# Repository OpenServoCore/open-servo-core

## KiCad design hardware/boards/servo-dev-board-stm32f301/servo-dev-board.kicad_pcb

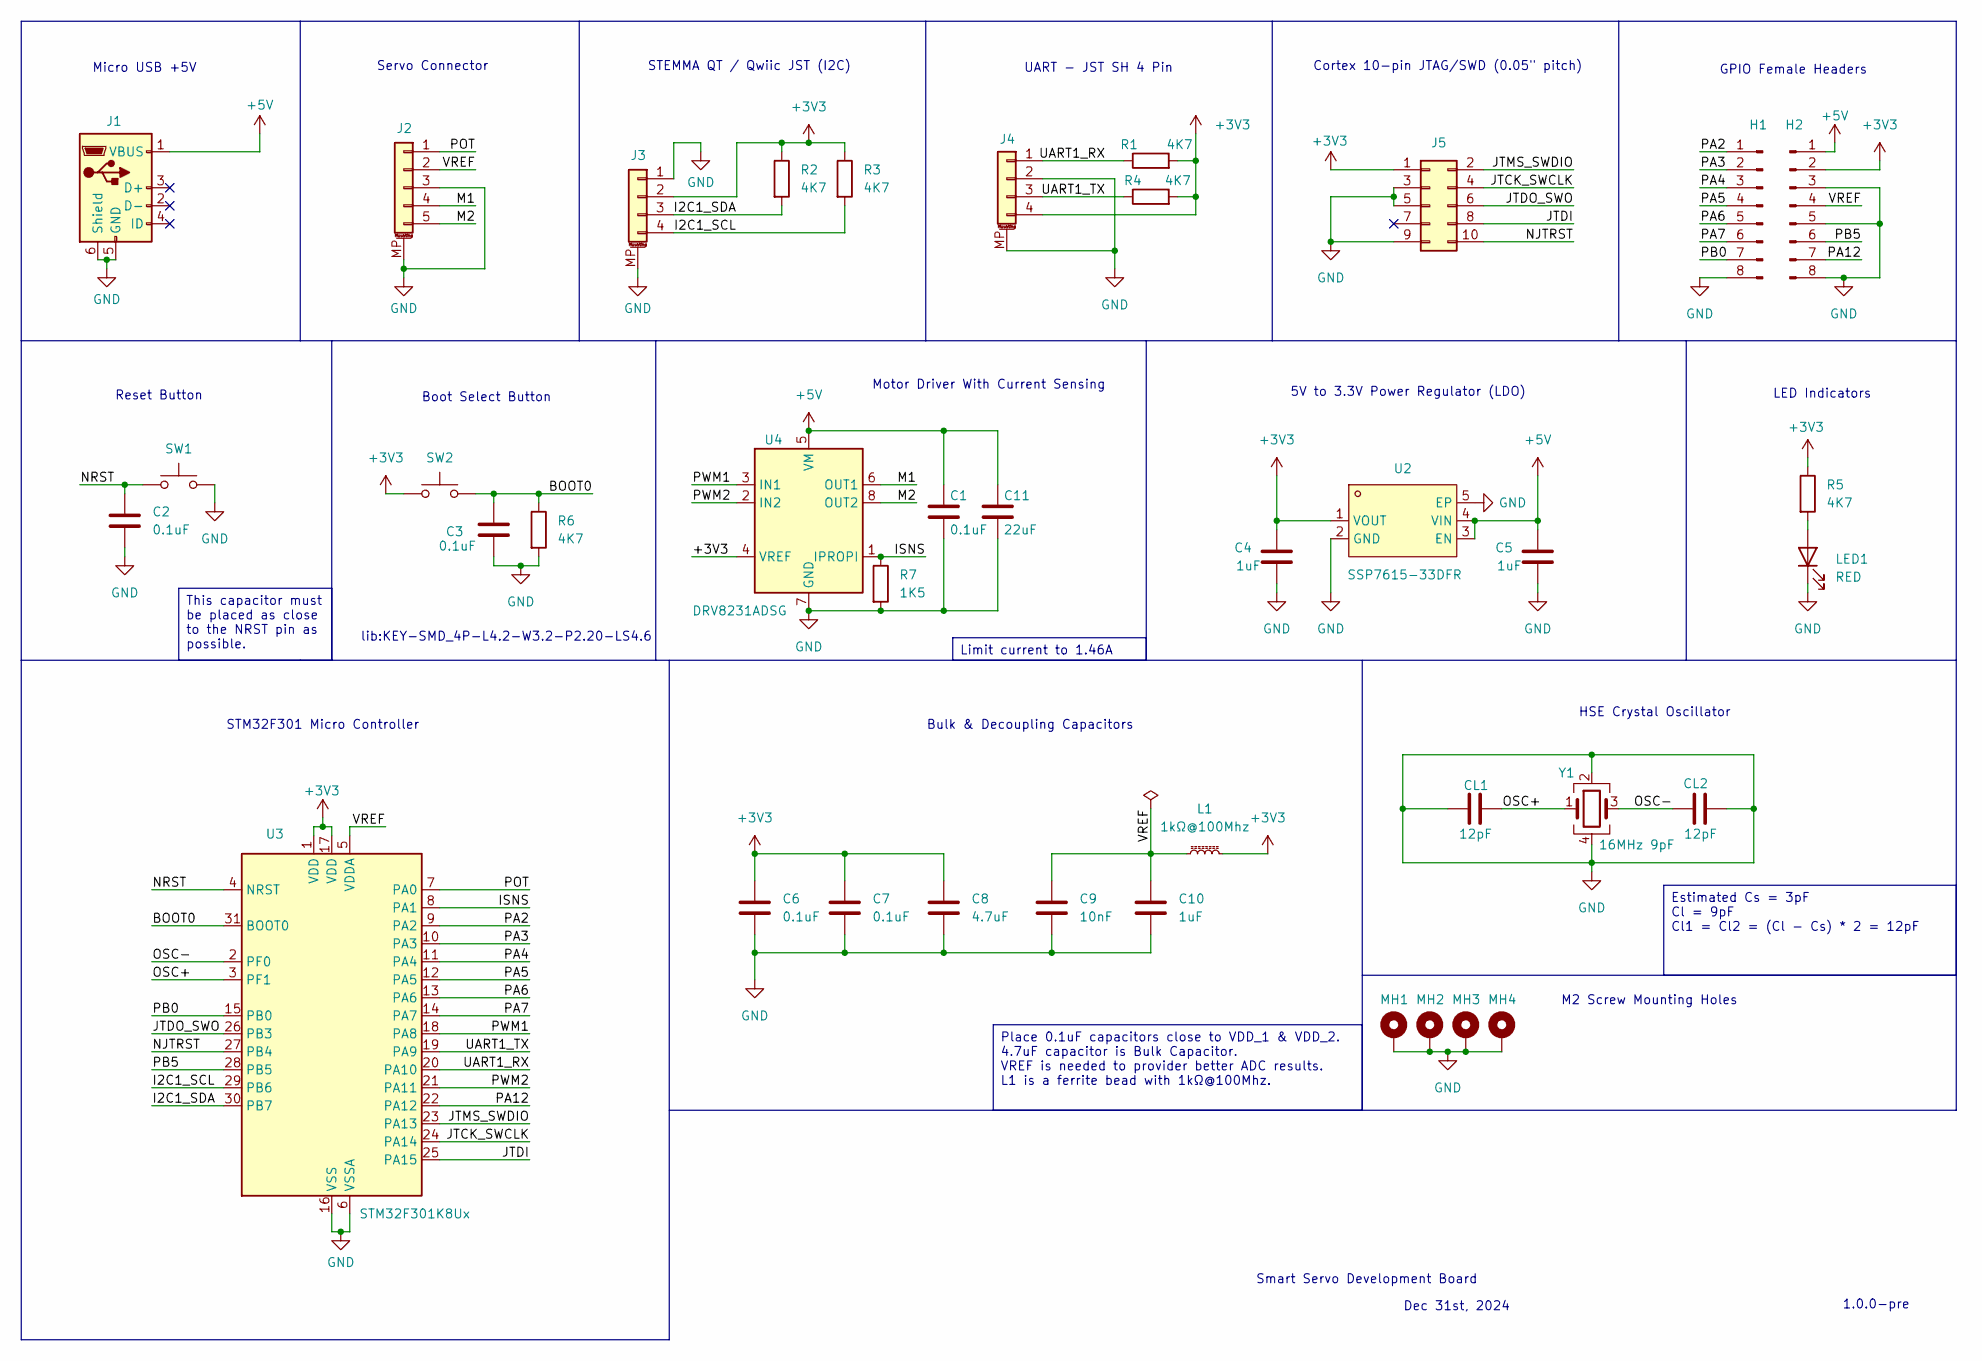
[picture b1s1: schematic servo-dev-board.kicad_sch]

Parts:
C1, C2, C3, C6, C7: 0.1uF; C_0402_1005Metric; LCSC C1525
C4, C5, C10: 1uF; C_0402_1005Metric; LCSC C52923
C8: 4.7uF; C_0603_1608Metric; LCSC C19666
C9: 10nF; C_0402_1005Metric; LCSC C15195
C11: 22uF; C_0603_1608Metric; LCSC C59461
CL1, CL2: 12pF; C_0402_1005Metric; LCSC C1547
H1, H2: Conn_01x08_Pin; PinHeader_1x08_P2.54mm_Vertical; LCSC C6332201
J1: USB_B_Micro; USB_Micro-B_Amphenol_10118194-0001LF_Horizontal; LCSC C428495
J2: Conn_01x05_MountingPin; JST_ZH_B5B-ZR-SM4-TF_1x05-1MP_P1.50mm_Vertical; LCSC C265440
J3, J4: Conn_01x04_MountingPin; JST_SH_BM04B-SRSS-TB_1x04-1MP_P1.00mm_Vertical; LCSC C160390
J5: Conn_02x05_Odd_Even; IDC-TH_10P-P1.27-X1270WV-2X05A-6TV01; LCSC C2962225
L1: 1kΩ@100Mhz; L_0402_1005Metric; LCSC C76883
LED1: RED; LED_0603_1608Metric; LCSC C2286
MH1, MH2, MH3, MH4: MountingHole_Pad_MP; MountingHole_2.2mm_M2_Pad_Via
R1, R2, R3, R4, R5, R6: 4K7; R_0402_1005Metric; LCSC C25792
R7: 1K5; R_0402_1005Metric; LCSC C25867
SW1, SW2: SW_Push; SW_SPST_PTS810; LCSC C221895
U2: SSP7615-33DFR; UDFN-4-1EP_1x1mm_P0.65mm_EP0.48x0.48mm; LCSC Part C3011523
U3: STM32F301K8Ux; QFN-32-1EP_5x5mm_P0.5mm_EP3.45x3.45mm; LCSC C111684
U4: DRV8231ADSG; WSON-8-1EP_2x2mm_P0.5mm_EP0.9x1.6mm
Y1: 16MHz 9pF; Crystal_SMD_3225-4Pin_3.2x2.5mm; LCSC C13738

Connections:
+3V3: C4.2, C6.2, C7.2, C8.2, H2.2, J3.2, J4.4, J5.1, L1.2, R1.2, R2.1, R3.1, R4.2, R5.1, SW2.1, U2.1 (VOUT), U3.1 (VDD), U3.17 (VDD), U4.4 (VREF)
+5V: C1.2, C5.2, C11.2, H2.1, J1.1 (VBUS), U2.3 (EN), U2.4 (VIN), U4.5 (VM)
/BOOT0: C3.1, R6.1, SW2.2, U3.31 (BOOT0)
/I2C1_SCL: J3.4, R3.2, U3.29 (PB6)
/I2C1_SDA: J3.3, R2.2, U3.30 (PB7)
/ISNS: R7.1, U3.8 (PA1), U4.1 (IPROPI)
/JTCK_SWCLK: J5.4, U3.24 (PA14)
/JTDI: J5.8, U3.25 (PA15)
/JTDO_SWO: J5.6, U3.26 (PB3)
/JTMS_SWDIO: J5.2, U3.23 (PA13)
/M1: J2.4, U4.6 (OUT1)
/M2: J2.5, U4.8 (OUT2)
/NJTRST: J5.10, U3.27 (PB4)
/NRST: C2.2, SW1.1, U3.4 (NRST)
/OSC+: CL1.1, U3.3 (PF1), Y1.1
/OSC-: CL2.2, U3.2 (PF0), Y1.3
/PA2: H1.1, U3.9 (PA2)
/PA3: H1.2, U3.10 (PA3)
/PA4: H1.3, U3.11 (PA4)
/PA5: H1.4, U3.12 (PA5)
/PA6: H1.5, U3.13 (PA6)
/PA7: H1.6, U3.14 (PA7)
/PA12: H2.7, U3.22 (PA12)
/PB0: H1.7, U3.15 (PB0)
/PB5: H2.6, U3.28 (PB5)
/POT: J2.1, U3.7 (PA0)
/PWM1: U3.18 (PA8), U4.3 (IN1)
/PWM2: U3.21 (PA11), U4.2 (IN2)
/UART1_RX: J4.1, R1.1, U3.20 (PA10)
/UART1_TX: J4.3, R4.1, U3.19 (PA9)
/VREF: C9.2, C10.2, H2.4, J2.2, L1.1, U3.5 (VDDA)
GND: C1.1, C2.1, C3.2, C4.1, C5.1, C6.1, C7.1, C8.1, C9.1, C10.1, C11.1, CL1.2, CL2.1, H1.8, H2.3, H2.5, H2.8, J1.5 (GND), J1.6 (Shield), J2.3, J2.MP (MountPin), J3.1, J3.MP (MountPin), J4.2, J4.MP (MountPin), J5.3, J5.5, J5.9, LED1.1 (K), MH1.1, MH2.1, MH3.1, MH4.1, R6.2, R7.2, SW1.2, U2.2 (GND), U2.5 (EP), U3.6 (VSSA), U3.16 (VSS), U3.32 (VSS), U3.33 (VSS), U4.7 (GND), U4.9 (GND), Y1.2, Y1.4
unnamed: LED1.2 (A), R5.2

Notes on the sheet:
Cortex 10-pin JTAG/SWD (0.05" pitch)
Dec 31st, 2024
Reset Button
Smart Servo Development Board
STM32F301 Micro Controller
Boot Select Button
Servo Connector
Bulk & Decoupling Capacitors
GPIO Female Headers
1.0.0-pre
5V to 3.3V Power Regulator (LDO)
LED Indicators
Micro USB +5V
M2 Screw Mounting Holes
UART - JST SH 4 Pin
STEMMA QT / Qwiic JST (I2C)
HSE Crystal Oscillator
lib:KEY-SMD_4P-L4.2-W3.2-P2.20-LS4.6
Motor Driver With Current Sensing
This capacitor must be placed as close to the NRST pin as possible.
Place 0.1uF capacitors close to VDD_1 & VDD_2. 4.7uF capacitor is Bulk Capacitor. VREF is needed to provider better ADC results. L1 is a ferrite bead with 1kΩ@100Mhz.
Limit current to 1.46A
Estimated Cs = 3pF Cl = 9pF Cl1 = Cl2 = (Cl - Cs) * 2 = 12pF

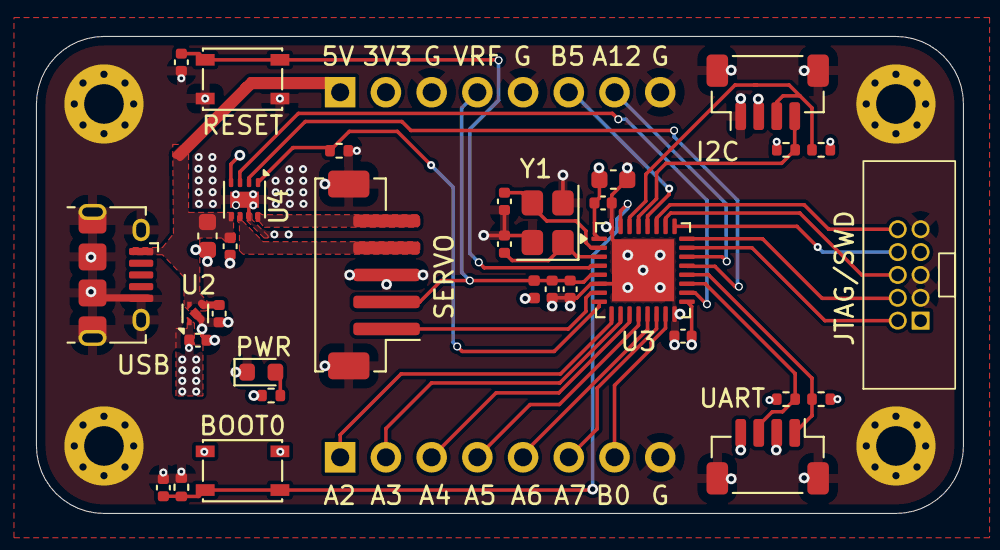
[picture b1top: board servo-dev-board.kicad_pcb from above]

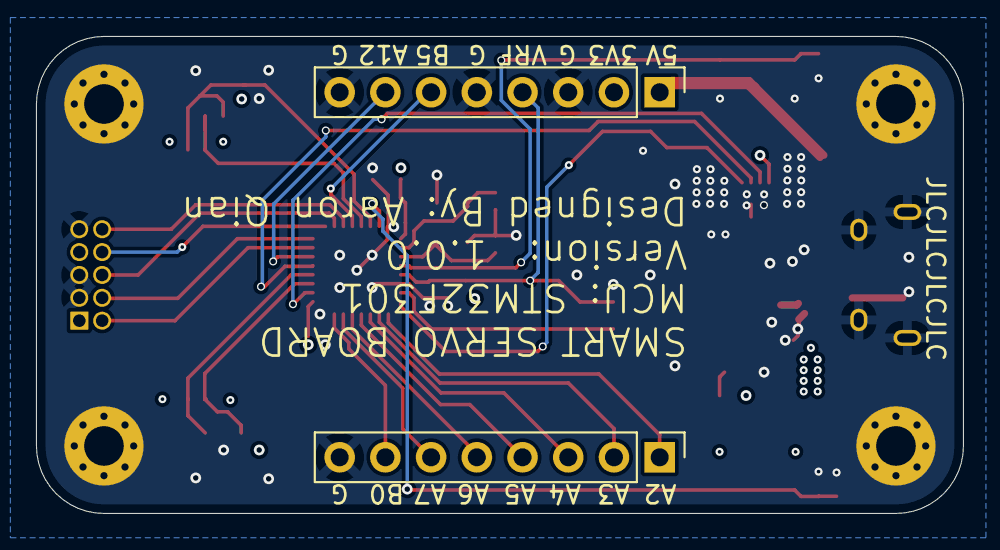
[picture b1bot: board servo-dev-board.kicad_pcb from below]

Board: 4 copper layers, 51.5 x 26.5 mm, 39 parts (2 on the bottom side), 33 nets.

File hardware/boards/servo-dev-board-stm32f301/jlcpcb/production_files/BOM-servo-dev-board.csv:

Comment,Designator,Footprint,LCSC,Quantity
0.1uF,"C1,C2,C3,C6,C7",C_0402_1005Metric,C1525,5
10nF,C9,C_0402_1005Metric,C15195,1
12pF,"CL1,CL2",C_0402_1005Metric,C1547,2
16MHz 9pF,Y1,Crystal_SMD_3225-4Pin_3.2x2.5mm,C13738,1
1K5,R7,R_0402_1005Metric,C25867,1
1kΩ@100Mhz,L1,L_0402_1005Metric,C76883,1
1uF,"C10,C4,C5",C_0402_1005Metric,C52923,3
22uF,C11,C_0603_1608Metric,C59461,1
4.7uF,C8,C_0603_1608Metric,C19666,1
4K7,"R1,R2,R3,R4,R5,R6",R_0402_1005Metric,C25792,6
Conn_01x04_MountingPin,"J3,J4",JST_SH_BM04B-SRSS-TB_1x04-1MP_P1.00mm_Vertical,C160390,2
Conn_01x05_MountingPin,J2,JST_ZH_B5B-ZR-SM4-TF_1x05-1MP_P1.50mm_Vertical,C265440,1
Conn_01x08_Pin,"H1,H2",PinHeader_1x08_P2.54mm_Vertical,C6332201,2
Conn_02x05_Odd_Even,J5,IDC-TH_10P-P1.27-X1270WV-2X05A-6TV01,C2962225,1
DRV8231ADSGR,U1,WSON-8-1EP_2x2mm_P0.5mm_EP0.9x1.6mm,C5139865,1
RED,LED1,LED_0603_1608Metric,C2286,1
SSP7615-33DFR,U2,UDFN-4-1EP_1x1mm_P0.65mm_EP0.48x0.48mm,C3011523,1
STM32F301K8Ux,U3,QFN-32-1EP_5x5mm_P0.5mm_EP3.45x3.45mm,C111684,1
SW_Push,"SW1,SW2",SW_SPST_PTS810,C221895,2
USB_B_Micro,J1,USB_Micro-B_Amphenol_10118194-0001LF_Horizontal,C428495,1

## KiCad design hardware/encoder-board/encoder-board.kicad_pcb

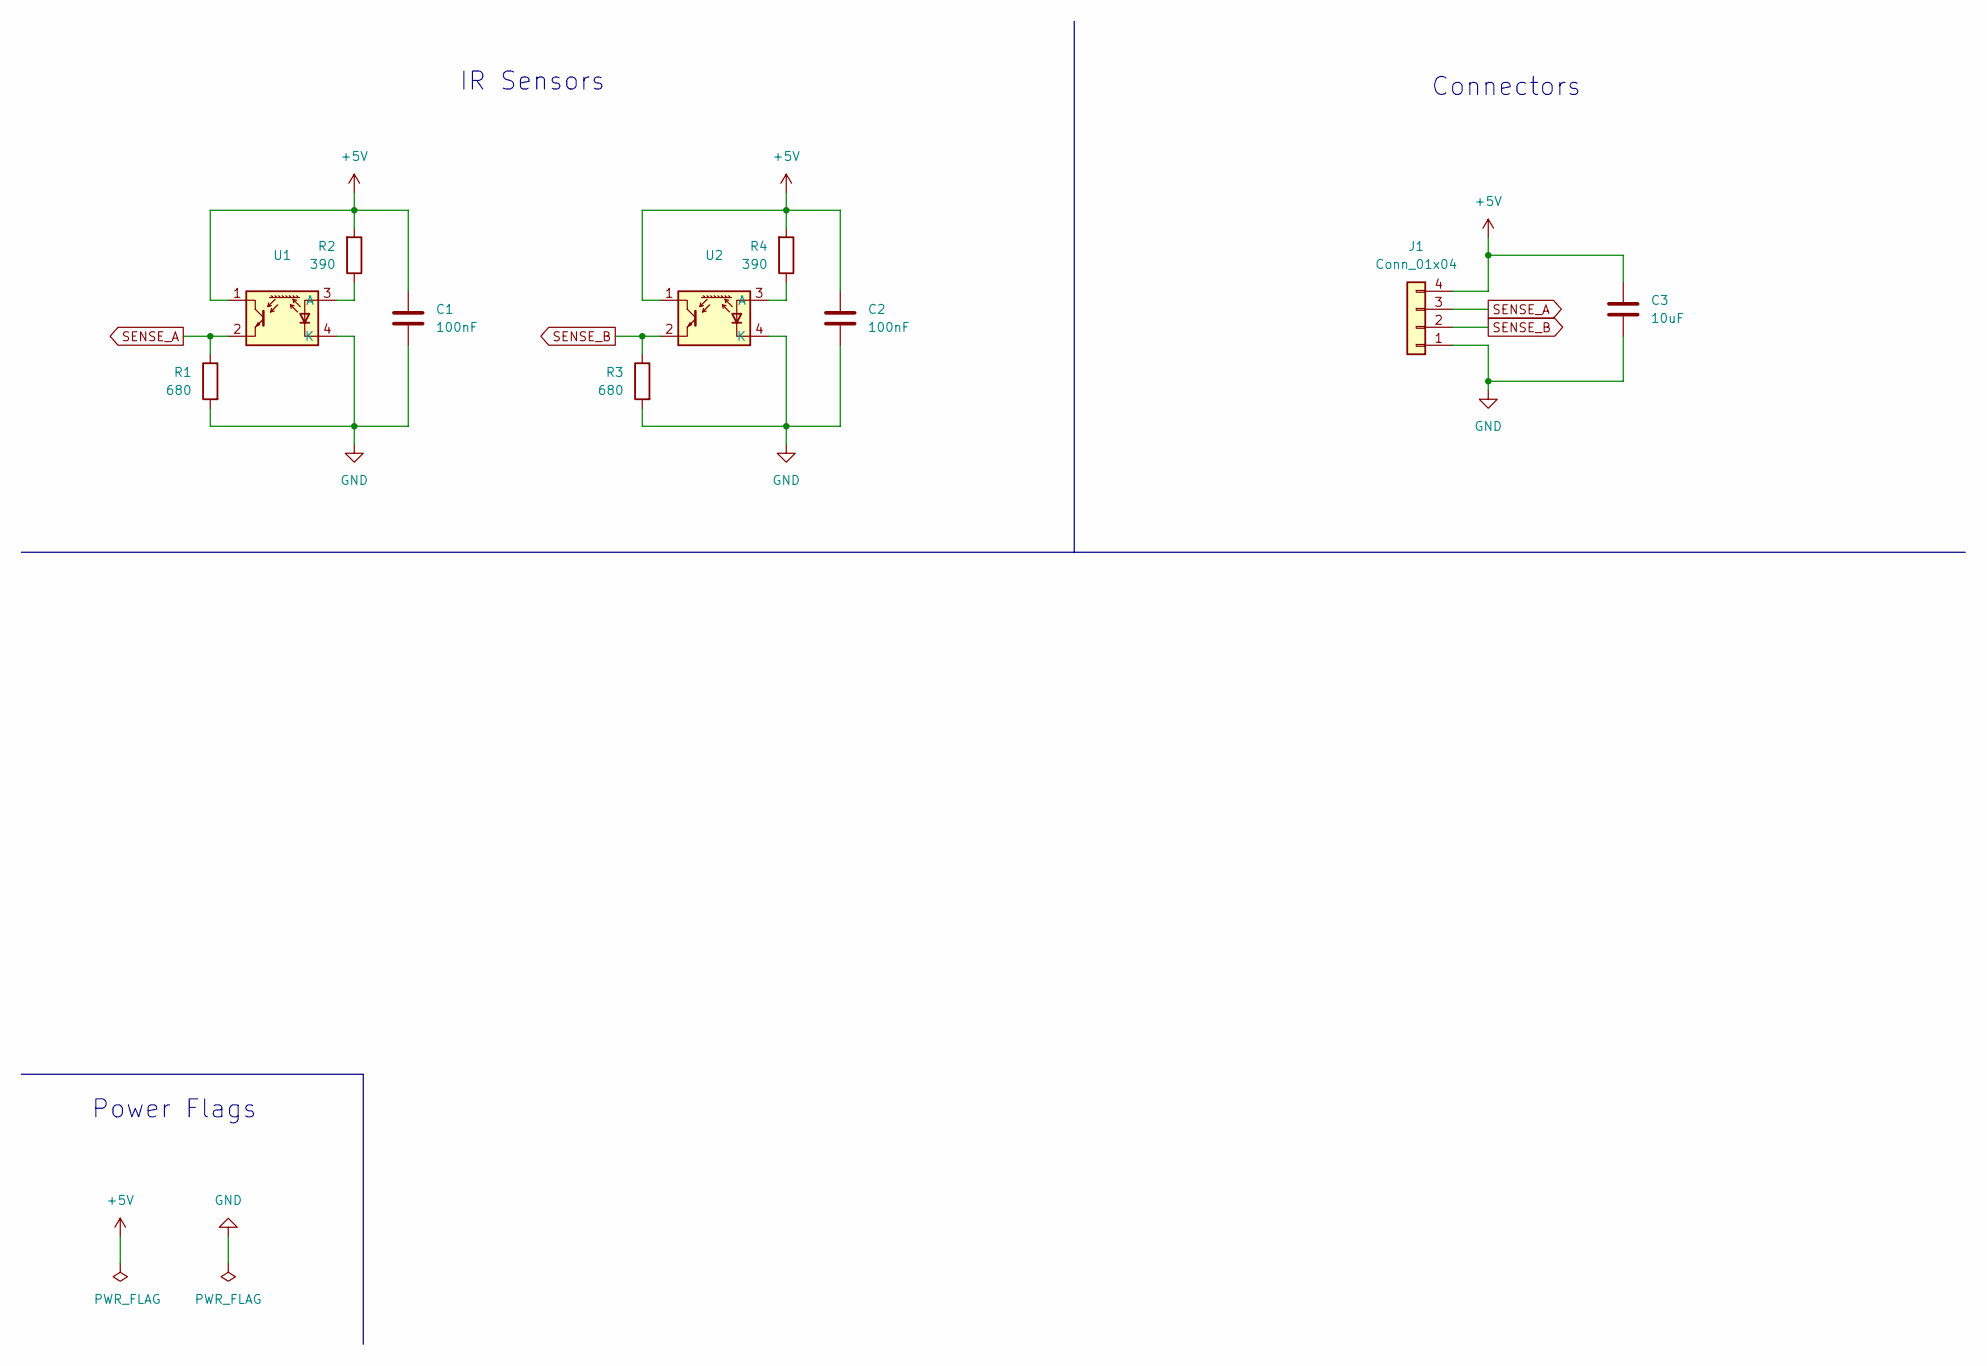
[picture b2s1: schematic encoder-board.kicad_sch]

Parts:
C1, C2: 100nF; C_0805_2012Metric_Pad1.18x1.45mm_HandSolder
C3: 10uF; C_0805_2012Metric_Pad1.18x1.45mm_HandSolder
J1: Conn_01x04; PinHeader_1x04_P2.54mm_Vertical; LCSC C780062
R1, R3: 680; R_0805_2012Metric_Pad1.20x1.40mm_HandSolder; LCSC C22548
R2, R4: 390; R_0805_2012Metric_Pad1.20x1.40mm_HandSolder; LCSC C125923
U1, U2: ITR1204SR10A_TR(BY); OPTO-SMD-4_ITR1204SR10A; LCSC C475373

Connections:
+5V: C1.1, C2.1, C3.1, J1.4, R2.2, R4.2, U1.1, U2.1
GND: C1.2, C2.2, C3.2, J1.1, R1.2, R3.2, U1.4 (K), U2.4 (K)
unnamed: R2.1, U1.3 (A)
unnamed: R4.1, U2.3 (A)
SENSE_A: J1.3, R1.1, U1.2
SENSE_B: J1.2, R3.1, U2.2

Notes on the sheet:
IR Sensors
Connectors
Power Flags

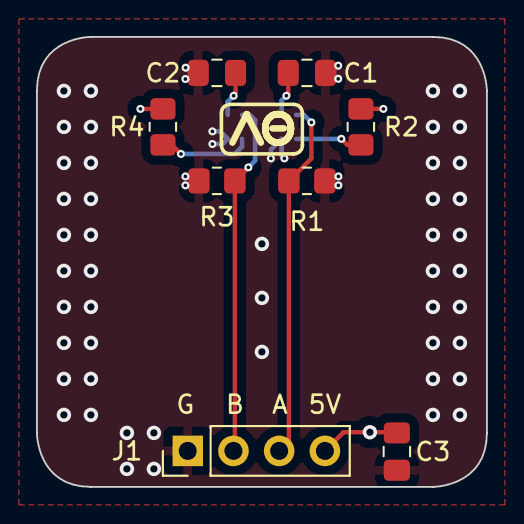
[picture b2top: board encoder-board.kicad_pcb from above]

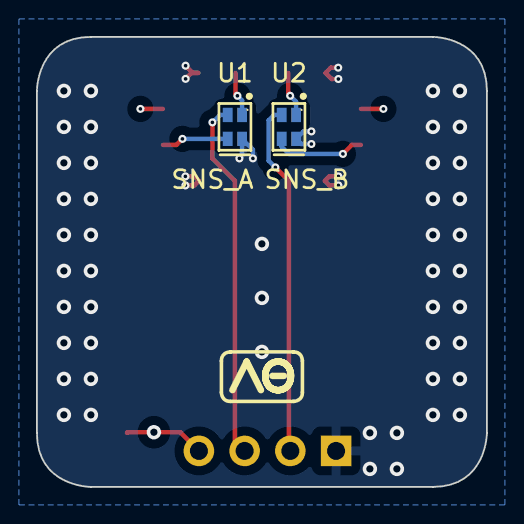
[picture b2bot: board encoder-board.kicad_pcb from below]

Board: 4 copper layers, 25.0 x 25.0 mm, 10 parts (2 on the bottom side), 6 nets.

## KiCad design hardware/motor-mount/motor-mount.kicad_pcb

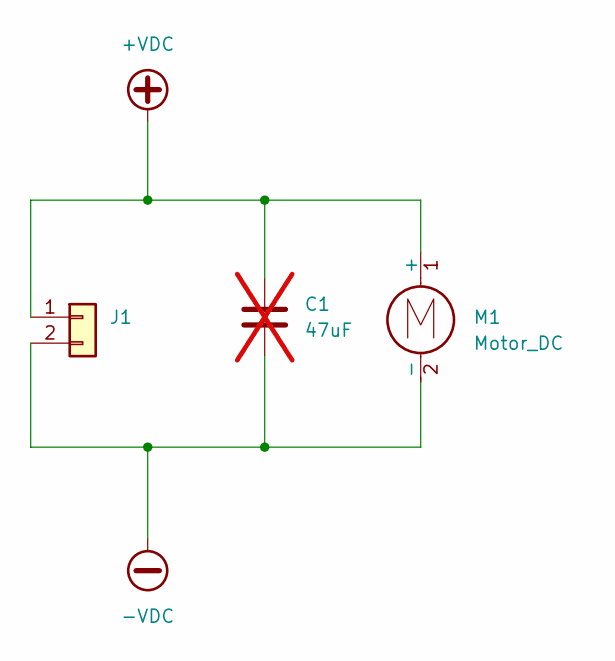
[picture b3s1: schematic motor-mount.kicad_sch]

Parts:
C1: 47uF; C_1206_3216Metric; not fitted
J1: PinHeader_1x02_P2.54mm_Vertical
M1: Motor_DC; SG90_Motor

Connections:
+VDC: C1.1, J1.1, M1.1 (+)
-VDC: C1.2, J1.2, M1.2 (-)

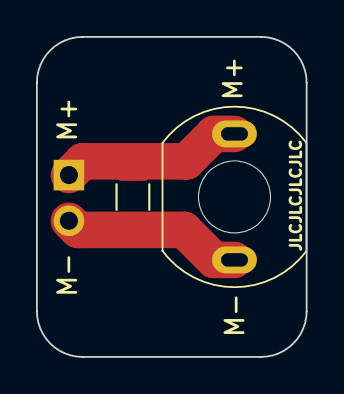
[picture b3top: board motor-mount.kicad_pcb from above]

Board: 2 copper layers, 15.0 x 17.8 mm, 3 parts (1 on the bottom side), 2 nets.
